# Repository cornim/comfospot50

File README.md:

<!-- SPDX-FileCopyrightText: 2026 cornim -->
<!-- SPDX-License-Identifier: CC-BY-SA-4.0 -->

# ComfoSpot 50 Home Assistant integration

This project integrates a ComfoSpot 50 into Home Assistant through a custom
ESPHome component and a custom-designed PCB board. The component connects an
ESP32-C3 to the existing panel, reading its LEDs and electrically simulating
short and long presses of the `+` and `-` buttons.

The component is in `components/comfospot/`. Complete ESPHome examples are in
`examples/`, installation and troubleshooting documentation is in `docs/`, and
wiring and the controller board design are in `hardware/`.

## Installation

See [`docs/installation.md`](docs/installation.md) for software flashing, board
power selection, hardware installation, security, and safety instructions.

## Safety and no warranty

This project is provided "as is", without warranty of any kind, express or
implied, including but not limited to warranties of merchantability, fitness
for a particular purpose, safety, and non-infringement. Use of this project
may involve electrical, fire, ventilation, property-damage, personal-injury,
or equipment-damage risks. You are responsible for verifying the design,
electrical compatibility, isolation, installation, operation, and compliance
with applicable laws and regulations.

Do not connect this circuit to a ventilation appliance or mains-related
equipment unless the installation has been reviewed and performed by a
suitably qualified person. Verify voltage levels, current limits, isolation,
grounding, enclosure requirements, and failure behavior before construction or
use. This project is not a safety control and must not be used where its
failure could create an unsafe condition.

## Unofficial project

This is an independent project and is not affiliated with, endorsed by, or
approved by Zehnder Group. "Zehnder" and "ComfoSpot" are trademarks of their
respective owners and are used only to identify the compatible product.

The original idea for this project and the reverse engineering of the ComfoSpot
50 were done by [lorenzspenger](https://github.com/lorenzspenger) in the
[`comfospot-50`](https://github.com/lorenzspenger/comfospot-50) project. This
repository's implementation was built from scratch because the original project
does not support standby mode.

## Fan levels

The fan exposes four active levels plus standby:

- `0`: standby, fans off
- `1` through `4`: the four ComfoSpot fan levels

In Home Assistant, standby is represented by the fan being off. The diagnostic
`Current Fan Speed` sensor reports the last confirmed numeric level `0` through
`4`. It remains unavailable only while the panel's display state is ambiguous,
such as immediately after boot with all LEDs off; it keeps reporting the last
known active speed while the display is temporarily dark for energy-saving mode.

The component reads the physical panel during boot and does not turn the unit
on automatically. Physical short button presses are synchronized back to Home
Assistant. Remote commands read and validate the panel directly, retrying when
the first press only wakes a sleeping display. Direction changes use the
observed panel marker and a bounded long-press operation. Filter runtime counts
confirmed active fan time and is persisted periodically and after a confirmed
filter reset.

## Hardware

The controller board design and detailed panel wiring documentation are in
[`hardware/README.md`](hardware/README.md) and
[`hardware/wiring.md`](hardware/wiring.md).

## Getting hardware

Detailed instructions for ordering the controller board are in
[`hardware/HOW_TO_ORDER.md`](hardware/HOW_TO_ORDER.md). The minimum
order is five boards, so if you need fewer boards, or if you have additional
boards to sell, feel free to open an issue in this repository to arrange a
purchase or sale.

## ESPHome configuration

The example downloads the component from this repository's `main` branch:

```yaml
external_components:
  - source:
      type: git
      url: https://github.com/cornim/comfospot50
      ref: main
    components: [comfospot]
```

See `examples/comfospot.yaml` for a complete example. It requires encrypted
API access, an OTA password, Wi-Fi credentials, and a non-empty fallback access
point password supplied through a local `examples/secrets.yaml`. Never commit
that file or any other deployment secrets.

The example declares the firmware project as `cornim.comfospot50`, version
`0.9.1`, using `esphome.project`. ESPHome embeds this metadata in the firmware
and reports it through logs, mDNS, and the native API. This is separate from
the ESPHome version required to compile the configuration.

## Building and testing

Build and run the host-side tests with:

```text
cmake -S . -B build
cmake --build build
ctest --test-dir build --output-on-failure
```

The live ESPHome API test runner is an optional Python end-to-end test suite in
`tests/e2e_comfospot.py`. It connects to a flashed ComfoSpot device over the
native ESPHome API, discovers its entities, exercises fan controls and state
reporting, and records a test report and device logs. It requires the
development dependency listed in `requirements-dev.txt`. The runner uses
credentials supplied through environment variables and never stores the API key
in test artifacts. See [`docs/e2e-testing.md`](docs/e2e-testing.md) for setup
and usage.

## Repository licensing

- ESPHome component source and tests: `GPL-3.0-or-later`.
- Project-authored schematic, PCB layout, wiring diagram, and hardware design:
  `CERN-OHL-S-2.0`.
- Project-authored documentation and timing notes: `CC-BY-SA-4.0`.
- Embedded component-library data and any other third-party material remain
  subject to their applicable terms; see `THIRD_PARTY_NOTICES.md`.

The project copyright holder is [`cornim`](https://github.com/cornim).
Licensing, security, and contribution questions are handled through GitHub for
this repository.

The license files are in `LICENSES/`. The root `LICENSE` is the GPLv3-or-later
license used for the software portion of the repository. The scoped notices in
the hardware and documentation directories define the other scopes.

No manufacturer datasheet PDFs or product manuals are distributed by this
repository. Consult the relevant manufacturer or distributor for current
documentation.

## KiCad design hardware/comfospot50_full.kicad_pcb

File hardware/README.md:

<!-- SPDX-FileCopyrightText: 2026 cornim -->
<!-- SPDX-License-Identifier: CERN-OHL-S-2.0 -->

# Hardware

The schematic and PCB in this directory are the project-authored controller
board design. The board is intended to interface an ESP32-C3 with the existing
ComfoSpot panel.
See [`wiring.md`](wiring.md) for the panel connections and electrical interface
notes.

## License scope

The project-authored schematic connectivity, PCB layout, routing, board
outline, wiring diagram, and related hardware documentation are released under
the CERN Open Hardware Licence Version 2 - Strongly Reciprocal, found in
`../LICENSES/CERN-OHL-S-2.0.txt`.

The KiCad files contain embedded component symbols and footprints selected from
the JLCPCB/LCSC/EasyEDA component ecosystem and Würth's component library.
Those embedded third-party elements are not relicensed by the project license.
Their provenance and applicable terms are described in
`../THIRD_PARTY_NOTICES.md`.

The standard KiCad library elements used by the design remain subject to the
KiCad library license and its design exception.

The project copyright holder is [`cornim`](https://github.com/cornim).
Licensing and contribution questions can be handled through GitHub for this
repository.

Source location for the covered hardware design is the GitHub repository
containing this file. Preserve this source location and the applicable notices
when conveying the hardware design or a product made from it.

## Deliberate omissions

3D model references are not included in the public PCB file. This keeps the
design portable and avoids distributing model files that are not needed for
schematic review, PCB editing, or fabrication. The board remains a complete
2D KiCad design and retains its footprints, pads, nets, routing, vias, zones,
silkscreen, and outline.

Manufacturer datasheet PDFs are not included. Use the manufacturer or
distributor source for current component documentation. The LCSC identifiers
in the BOM are retained as manufacturing-selection information.

The `hardware/production/comfospot50_full.zip` archive contains Gerber and
drill fabrication output. It is generated output and does not contain the
component library or 3D model files.

## Safety and no warranty

The hardware is provided "as is", without warranty of any kind, express or
implied, including warranties of merchantability, fitness for a particular
purpose, safety, and non-infringement. Verify voltage levels, current limits,
isolation, grounding, enclosure requirements, creepage, clearance, and failure
behavior before construction or use. A qualified person must review and
perform any connection to an installed ventilation appliance or mains-related
equipment.

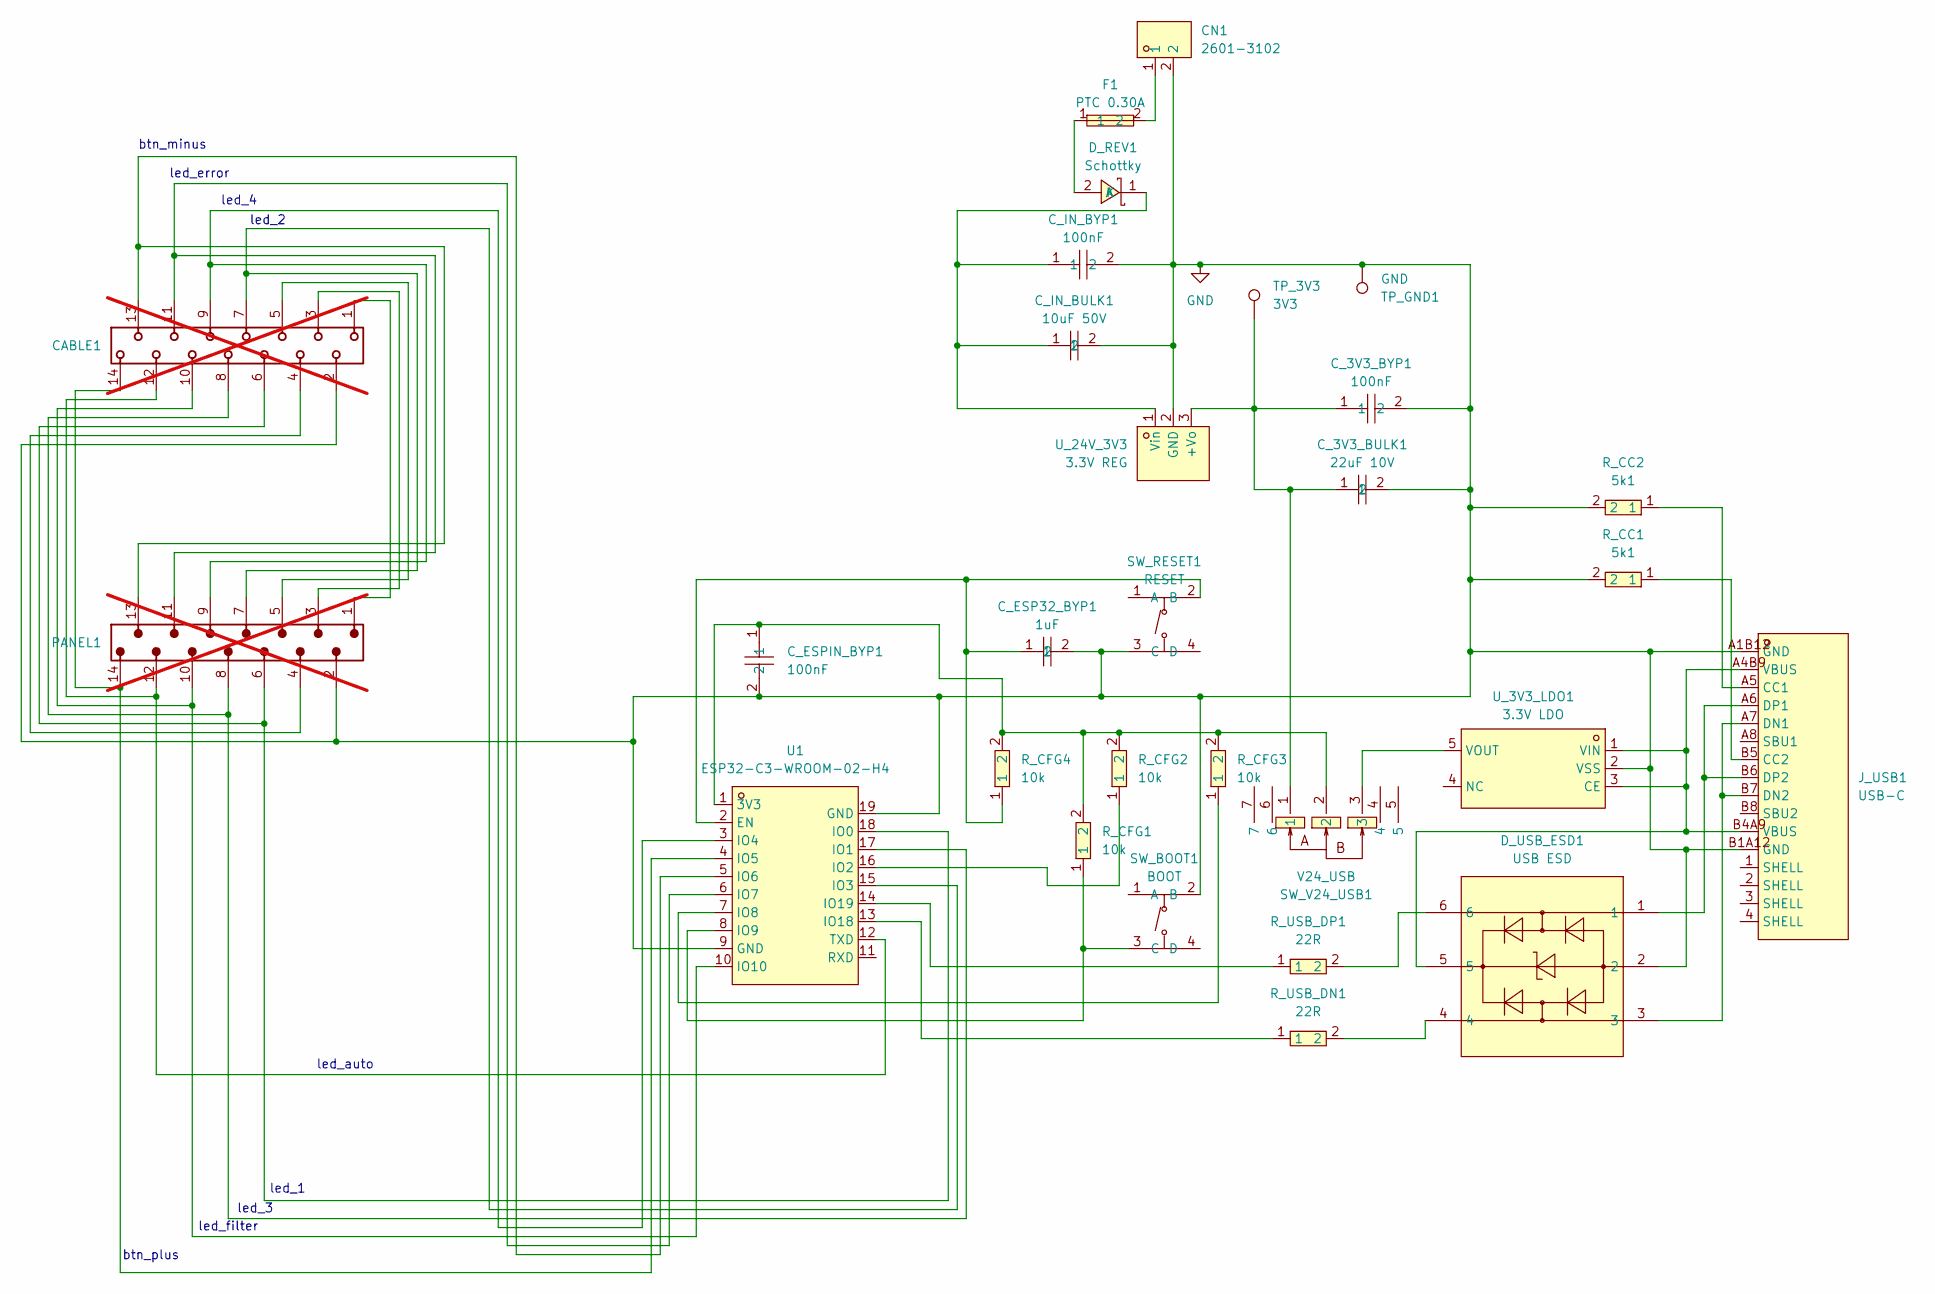
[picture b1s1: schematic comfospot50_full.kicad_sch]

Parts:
CABLE1: 14-pin F; J_Wurth_WR-MM_690368171472; Working Voltage (V (AC)) 250; not fitted
CN1: 2601-3102; CONN-TH_4P-P3.5-2601-3102; MPN 2601-3102; LCSC Part C20252913
C_3V3_BULK1: 22uF 10V; C1206; MPN CL31A226KPHNNNE; LCSC Part C5672
C_3V3_BYP1: 100nF; C0603; MPN CC0603KRX7R9BB104; LCSC Part C14663
C_ESP32_BYP1: 1uF; C0603; MPN CC0603KRX5R6BB105; LCSC Part C106214
C_ESPIN_BYP1: 100nF; C0603; MPN CC0603KRX7R9BB104; LCSC Part C14663
C_IN_BULK1: 10uF 50V; C1206; MPN CL31A106KBHNNNE; LCSC Part C13585
C_IN_BYP1: 100nF; C0603; MPN CC0603KRX7R9BB104; LCSC Part C14663
D_REV1: Schottky; SMA_L4.3-W2.6-LS5.2-RD; MPN SS110; LCSC Part C2482
D_USB_ESD1: USB ESD; SOT-23-6_L2.9-W1.6-P0.95-LS2.8-BL; MPN USBLC6-2SC6; LCSC Part C7519
F1: PTC 0.30A; FUSE-TH_L7.4-W3.0-P5.10-D0.6-S1.20; MPN RXEF030; LCSC Part C18384
J_USB1: USB-C; USB-C-SMD_TYPE-C16PIN; MPN TYPE-C16PIN; LCSC Part C393939
PANEL1: 14-pin M; J_Wurth_WR-MM_690357101472; not fitted
R_CC1, R_CC2: 5k1; R0603; MPN RMC06035.1K1%N; LCSC Part C269716
R_CFG1, R_CFG2, R_CFG3, R_CFG4: 10k; R0603; MPN 0603WAF1002T5E; LCSC Part C25804
R_USB_DN1: 22R; R0402; MPN RC0402FR-0722RL; LCSC Part C114765
R_USB_DP1: 22R; R0402; MPN RC0402FR-0722RL; LCSC Part C114765
SW_BOOT1: BOOT; SW-SMD_4P-L5.1-W5.1-P3.70-LS6.5-TL_H1.5; MPN TS-1187A-B-A-B; LCSC Part C318884
SW_RESET1: RESET; SW-SMD_4P-L5.1-W5.1-P3.70-LS6.5-TL_H1.5; MPN TS-1187A-B-A-B; LCSC Part C318884
SW_V24_USB1: V24_USB; SW-SMD_MK-12C02-G020; MPN MK-12C02-G020; LCSC Part C963206
TP_3V3: 3V3; TestPoint_Pad_D2.0mm
TP_GND1: GND; TestPoint_Pad_D2.0mm
U1: ESP32-C3-WROOM-02-H4; WIFIM-SMD_18P-L20.0-W18.0-P1.50; MPN ESP32-C3-WROOM-02-H4; LCSC Part C2944070
U_3V3_LDO1: 3.3V LDO; SOT-23-5_L3.0-W1.7-P0.95-LS2.8-BL; MPN ME6211C33M5G-N; LCSC Part C82942
U_24V_3V3: 3.3V REG; PWRM-TH_YLPTEC_K78XX-1000R3; MPN K7803-1000R3; LCSC Part C5369647

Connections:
GND: CABLE1.2, CN1.2, C_3V3_BULK1.2, C_3V3_BYP1.2, C_ESP32_BYP1.2, C_ESPIN_BYP1.2, C_IN_BULK1.2, C_IN_BYP1.2, D_USB_ESD1.2, J_USB1.A1B12 (GND), J_USB1.B1A12 (GND), PANEL1.2, R_CC1.2, R_CC2.2, SW_BOOT1.2 (B), SW_RESET1.3 (C), TP_GND1.1 (1_1), U1.9 (GND), U1.19 (GND), U_3V3_LDO1.2 (VSS), U_24V_3V3.2 (GND)
unnamed: CABLE1.1, PANEL1.1
unnamed: CABLE1.3, PANEL1.3
unnamed: CABLE1.4, PANEL1.4
unnamed: CABLE1.5, PANEL1.5
unnamed: CN1.1, F1.2
unnamed: D_REV1.2 (A), F1.1
unnamed: C_IN_BULK1.1, C_IN_BYP1.1, D_REV1.1 (K), U_24V_3V3.1 (Vin)
unnamed: D_USB_ESD1.4, R_USB_DN1.2
unnamed: D_USB_ESD1.6, R_USB_DP1.2
unnamed: J_USB1.A5 (CC1), R_CC2.1
unnamed: J_USB1.B5 (CC2), R_CC1.1
unnamed: D_USB_ESD1.3, J_USB1.A7 (DN1), J_USB1.B7 (DN2)
unnamed: D_USB_ESD1.1, J_USB1.A6 (DP1), J_USB1.B6 (DP2)
unnamed: R_CFG1.1, SW_BOOT1.3 (C), U1.8 (IO9)
unnamed: C_ESP32_BYP1.1, R_CFG4.1, SW_RESET1.2 (B), U1.2 (EN)
unnamed: C_ESPIN_BYP1.1, R_CFG1.2, R_CFG2.2, R_CFG3.2, R_CFG4.2, SW_V24_USB1.2, U1.1 (3V3)
unnamed: CABLE1.6, PANEL1.6, U1.18 (IO0)
unnamed: CABLE1.8, PANEL1.8, U1.17 (IO1)
unnamed: R_CFG2.1, U1.16 (IO2)
unnamed: CABLE1.7, PANEL1.7, U1.15 (IO3)
unnamed: CABLE1.9, PANEL1.9, U1.3 (IO4)
unnamed: CABLE1.14, PANEL1.14, U1.4 (IO5)
unnamed: CABLE1.13, PANEL1.13, U1.5 (IO6)
unnamed: CABLE1.11, PANEL1.11, U1.6 (IO7)
unnamed: R_CFG3.1, U1.7 (IO8)
unnamed: CABLE1.10, PANEL1.10, U1.10 (IO10)
unnamed: R_USB_DN1.1, U1.13 (IO18)
unnamed: R_USB_DP1.1, U1.14 (IO19)
unnamed: CABLE1.12, PANEL1.12, U1.12 (TXD)
unnamed: D_USB_ESD1.5, J_USB1.A4B9 (VBUS), J_USB1.B4A9 (VBUS), U_3V3_LDO1.1 (VIN), U_3V3_LDO1.3 (CE)
unnamed: SW_V24_USB1.3, U_3V3_LDO1.5 (VOUT)
unnamed: C_3V3_BULK1.1, C_3V3_BYP1.1, SW_V24_USB1.1, TP_3V3.1 (1_1), U_24V_3V3.3 (+Vo)

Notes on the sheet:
led_error
led_2
btn_minus
led_1
btn_plus
led_filter
led_auto
led_4
led_3

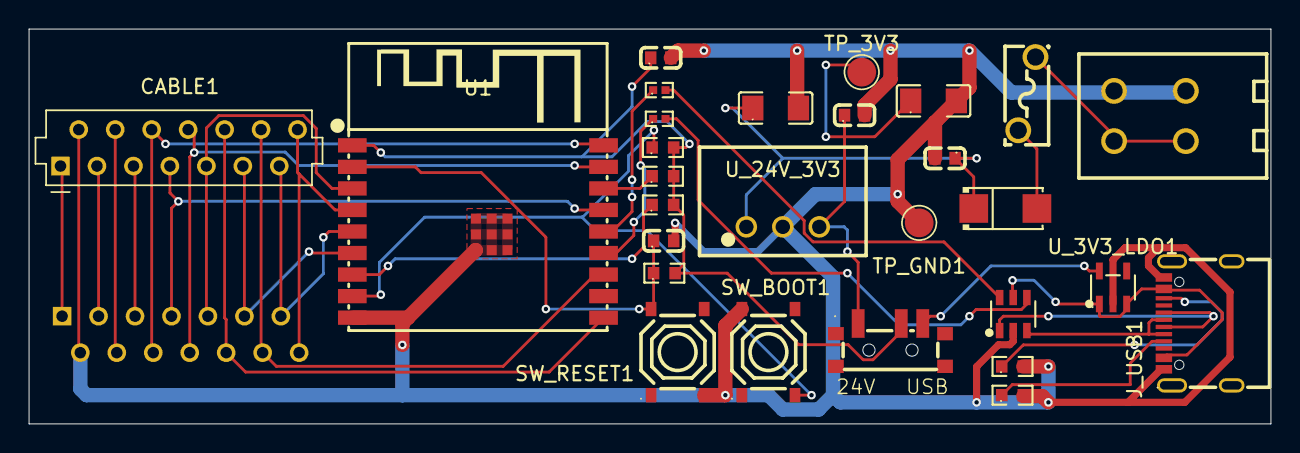
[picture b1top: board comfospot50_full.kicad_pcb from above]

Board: 2 copper layers, 86.5 x 27.5 mm, 29 parts (1 on the bottom side), 33 nets.
